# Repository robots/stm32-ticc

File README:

#STM32 based TICC

This project is based on TAPR's TICC project.

## Hardware

The frontend for time capture is copied from their schematic. Change has been done to input PICDIV that is responsible for coarse clock generation.

Original design uses pic12f675. For this design I have used pic12f1572. The software differences are only minor - few bank switch instructions. Hardware differense is almost none. Functional
difference is yet to be determined. But I dont think that the deterministic behavior of PIC has been changed.

Workhorse has been changed from ATMEGA to something more recent. I have used STM32F042.

This MCU has integrated 48MHz oscillator with clock recovery from USB, USB peripheral, lots of flash/ram for such simple project.

## Software

TICC presents on USB as ACM device. This works without any additional driver on linux. For windows i dont know - you will probably need ST's ACM driver. (google is your friend)

To connect use any terminal emulator you like - windows: realterm, teraterm, hyperterminal, ... for linux: minicom, screen, tio. Set speed to something reasonable (eg. 921600) and hit enter.

You should be presented with command line prompt ">".

Commands are:

help - prints help
reboot - reboots board
dfu - switches mcu to dfu mode. Carefull, you will need dfu-util to bring device back to live.
cfg - configuration submenu

cfg show - prints current configuration
cfg set xx blabla - sets variable "xx" to value "blabla"
cfg save - saves configuration to eeprom (not working yet)

Most configuration options are same as TICC, for more info refer to their documentation.

# Building
You will need gnuarm toolchain, gnu make and dfu-util.

Make sure that you have arm toolchain in PATH, enter "main" directory, and type "make bin".

To write the firmware to board use "dfu.sh" script. This script does two things: writes firmware and writes options to exit dfu mode.

# Credits
Software has been mostly written from scratch except for:
- usb stack, stdlibrary - from ST
- time interval calculation routines and TDC7200 driver  - from original TICC project, mostly rewritten or adapted for better readability - https://github.com/TAPR/TICC
- tfprintf - Copyright (C) 2004,2012  Kustaa Nyholm http://www.sparetimelabs.com/tinyprintf/index.html

Hardware:
- based on https://github.com/TAPR/TICC

# License
All files written by me are released to public domain. Use as you please. It would be nice to reference original repository if you do.

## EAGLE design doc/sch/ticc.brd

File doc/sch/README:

In this directory:

ticc.* - schematic/board layout for TICC
picdiv.* - schematic/board layout for simple PICDIV board.

There is absolutely no warranty and not support for these boards. While there are few working examples of this design I dont have time or resources for support.

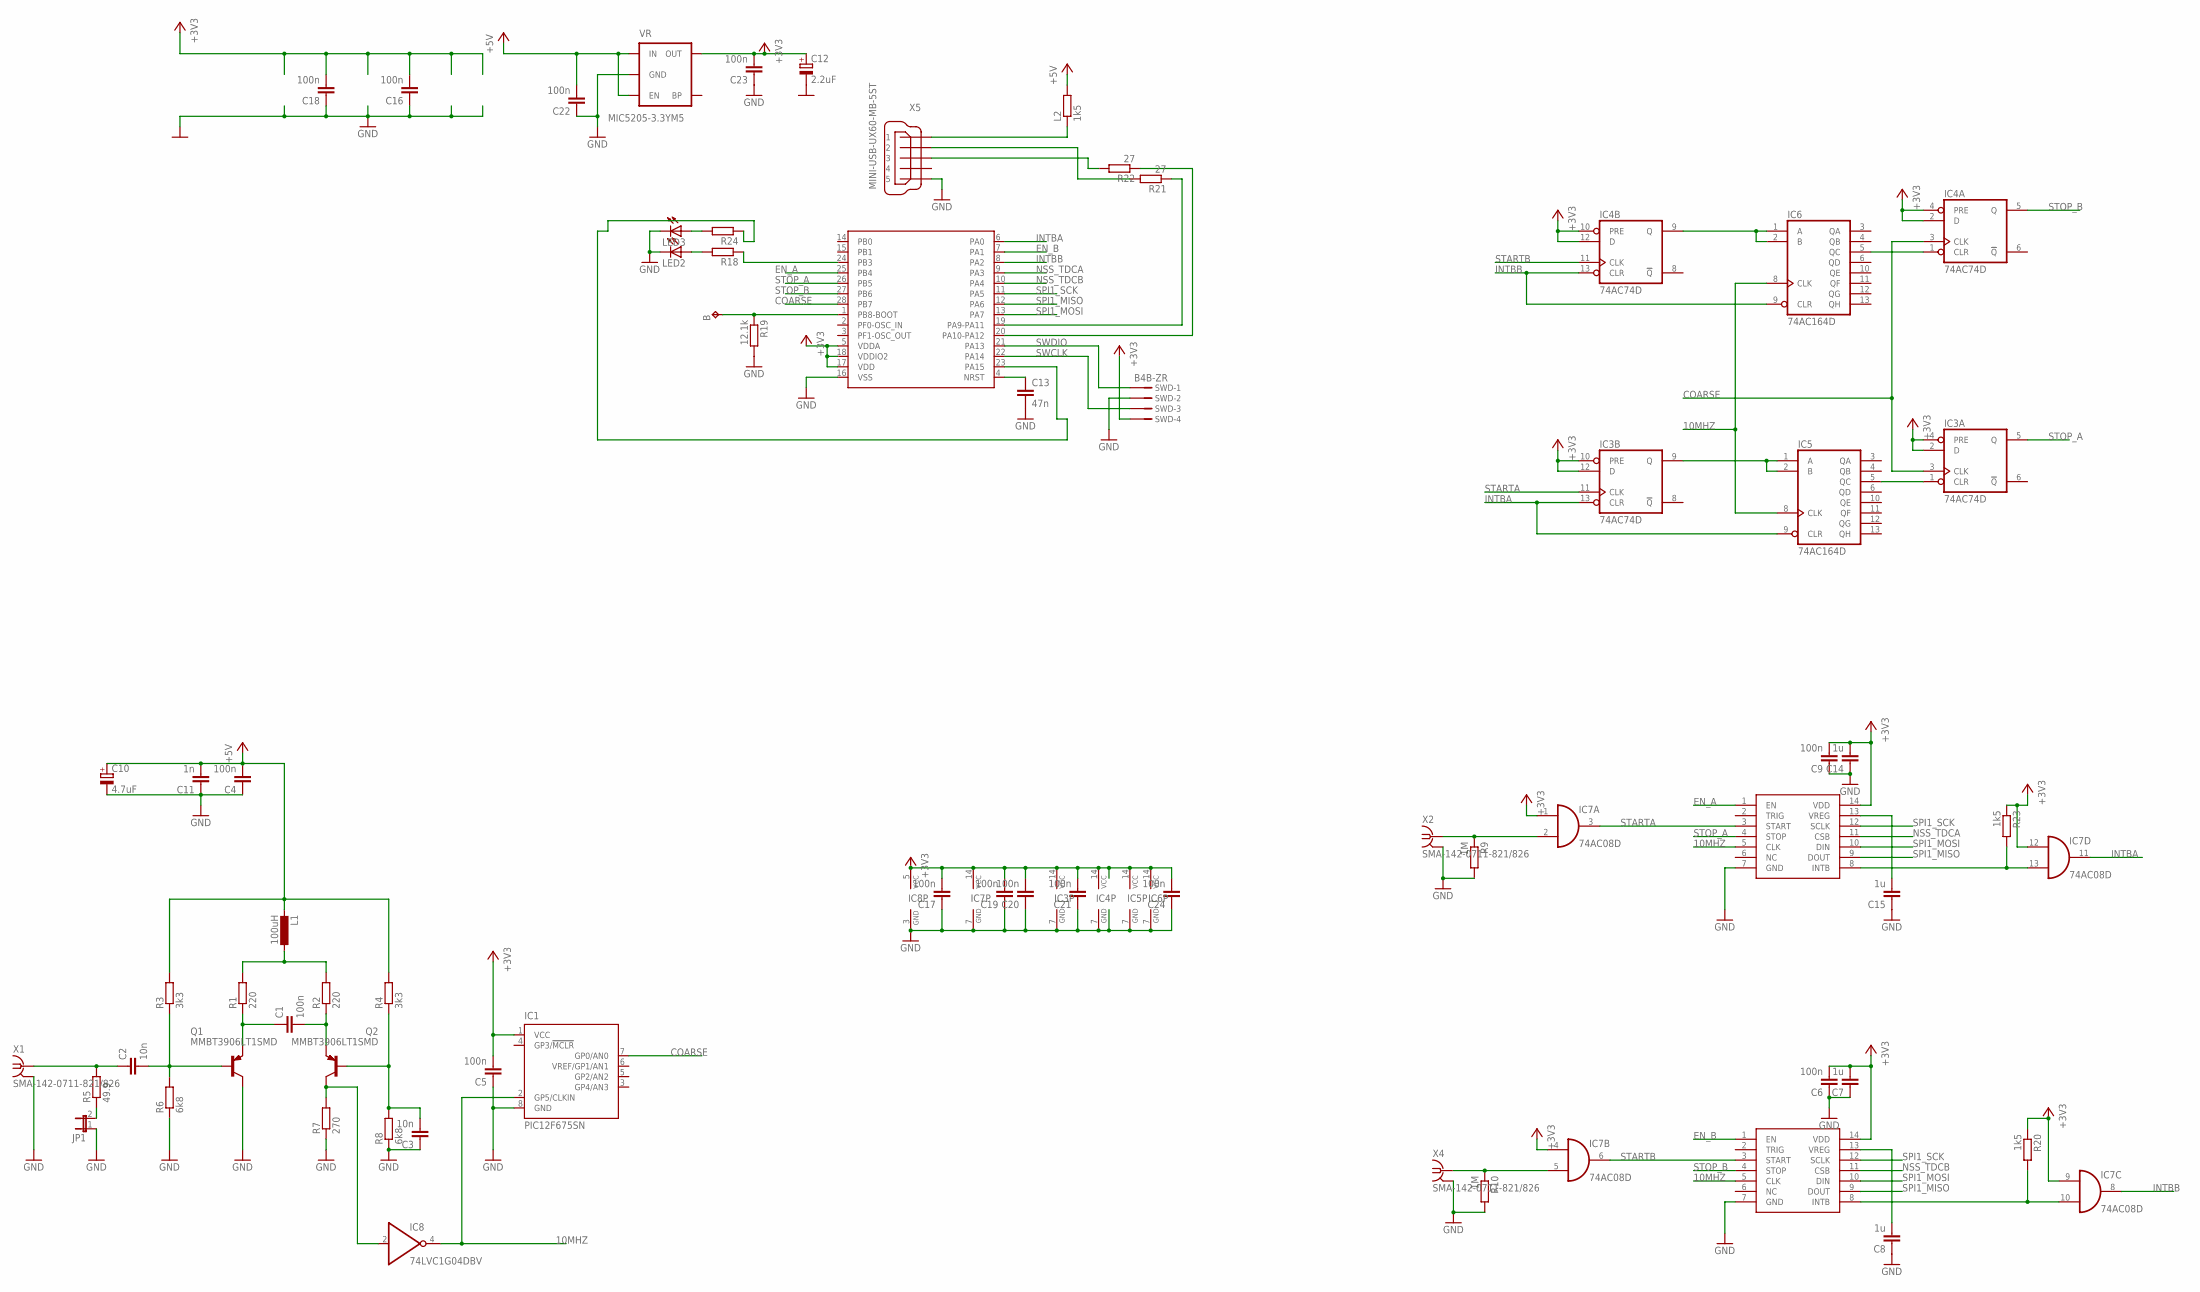
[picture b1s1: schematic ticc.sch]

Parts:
B: TPB1,27; B1,27
C1, C4, C5, C6, C9, C16, C17, C18, C19, C20, C21, C24: 100n; C0603
C2, C3: 10n; C0603
C7, C8, C14, C15: 1u; C0603
C10: 4.7uF; SMC_A
C11: 1n; C0603
C12: 2.2uF; SMC_A
C13: 47n; C0603
C22, C23: 100n; C0805K
IC1: PIC12F675SN; SO-08
IC3, IC4: 74AC74D; SO14
IC5, IC6: 74AC164D; SO14
IC7: 74AC08D; SO14
IC8: 74LVC1G04DBV; SOT23-5
JP1: JUMPER-2PTH; 1X02
L1: 100uH; L2012C
L2: 1k5; R0805
LED2, LED3: LEDCHIP-LED0805; CHIP-LED0805
Q1, Q2: MMBT3906LT1SMD; SOT23-BEC
R1, R2: 220; R0603
R3, R4: 3k3; R0603
R5: 49.9; R0603
R6, R8: 6k8; R0603
R7: 270; R0603
R9, R10: 1M; R0603
R18, R24: R-EU_R0603; R0603
R19: 12.1k; R0603
R20, R23: 1k5; R0603
R21, R22: 27; R0603
SWD: B4B-ZR
U$1: STM32F042G; QFN28
U$2, U$3: TDC7200; TSSOP14
VR: MIC5205-3.3YM5; SOT23-5
X1, X2, X4: SMA-142-0711-821/826; J502-ND-142-0711-821/826
X5: MINI-USB-UX60-MB-5ST; UX60-MB-5ST

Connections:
10MHZ: IC1.2 (GP5/CLKIN), IC5.8 (CLK), IC6.8 (CLK), IC8.4 (O), U$2.5 (CLK), U$3.5 (CLK)
+3V3: C5.2, C6.2, C7.2, C9.2, C12.+, C14.2, C16.2, C17.2, C18.2, C19.2, C20.2, C21.2, C23.2, C24.2, IC1.1 (VCC), IC3.2 (D), IC3.4 (PRE), IC3.10 (PRE), IC3.12 (D), IC3.14 (VCC), IC4.2 (D), IC4.4 (PRE), IC4.10 (PRE), IC4.12 (D), IC4.14 (VCC), IC5.14 (VCC), IC6.14 (VCC), IC7.1 (I0), IC7.4 (I0), IC7.9 (I0), IC7.12 (I0), IC7.14 (VCC), IC8.5 (VCC), R20.1, R23.1, SWD.4, U$1.5 (VDDA), U$1.17 (VDD), U$1.18 (VDDIO2), U$2.14 (VDD), U$3.14 (VDD), VR.5 (OUT)
+5V: C4.2, C10.+, C11.2, C22.2, L1.2, L2.2, R3.2, R4.2, VR.1 (IN), VR.3 (EN)
COARSE: IC1.7 (GP0/AN0), IC3.3 (CLK), IC4.3 (CLK), U$1.28 (PB7)
EN_A: U$1.25 (PB4), U$2.1 (EN)
EN_B: U$1.7 (PA1), U$3.1 (EN)
GND: C3.1, C4.1, C5.1, C6.1, C7.1, C8.1, C9.1, C10.-, C11.1, C12.-, C13.2, C14.1, C15.1, C16.1, C17.1, C18.1, C19.1, C20.1, C21.1, C22.1, C23.1, C24.1, IC1.8 (GND), IC3.7 (GND), IC4.7 (GND), IC5.7 (GND), IC6.7 (GND), IC7.7 (GND), IC8.3 (GND), JP1.1, LED2.C, LED3.C, Q1.C, R6.1, R7.1, R8.1, R9.2, R10.2, R19.2, SWD.2, U$1.16 (VSS), U$2.7 (GND), U$3.7 (GND), VR.2 (GND), X1.G@1 (GND), X1.G@2 (GND), X1.G@3 (GND), X1.G@4 (GND), X2.G@1 (GND), X2.G@2 (GND), X2.G@3 (GND), X2.G@4 (GND), X4.G@1 (GND), X4.G@2 (GND), X4.G@3 (GND), X4.G@4 (GND), X5.5
INTBA: IC3.13 (CLR), IC5.9 (CLR), IC7.11 (O), U$1.6 (PA0)
INTBB: IC4.13 (CLR), IC6.9 (CLR), IC7.8 (O), U$1.8 (PA2)
unnamed: C3.2, Q2.B, R4.1, R8.2
unnamed: JP1.2, R5.1
unnamed: C2.1, R5.2, X1.1
unnamed: C2.2, Q1.B, R3.1, R6.2
unnamed: L1.1, R1.2, R2.2
unnamed: C1.2, Q2.E, R2.1
unnamed: C1.1, Q1.E, R1.1
unnamed: R22.2, X5.3
unnamed: IC8.2 (I), Q2.C, R7.2
unnamed: IC7.2 (I1), R9.1, X2.1
unnamed: R21.2, X5.2
unnamed: IC7.5 (I1), R10.1, X4.1
unnamed: R18.1, U$1.24 (PB3)
unnamed: C15.2, U$2.13 (VREG)
unnamed: L2.1, X5.1
unnamed: R21.1, U$1.19 (PA9-PA11)
unnamed: IC3.1 (CLR), IC5.5 (QC)
unnamed: R22.1, U$1.20 (PA10-PA12)
unnamed: B.PP, R19.1, U$1.1 (PB8-BOOT)
unnamed: C13.1, U$1.4 (NRST)
unnamed: LED2.A, R18.2
unnamed: IC4.1 (CLR), IC6.5 (QC)
unnamed: IC3.9 (Q), IC5.1 (A), IC5.2 (B)
unnamed: IC4.9 (Q), IC6.1 (A), IC6.2 (B)
unnamed: R24.1, U$1.23 (PA15)
unnamed: IC7.10 (I1), R20.2, U$3.8 (INTB)
unnamed: IC7.13 (I1), R23.2, U$2.8 (INTB)
unnamed: LED3.A, R24.2
unnamed: C8.2, U$3.13 (VREG)
NSS_TDCA: U$1.9 (PA3), U$2.11 (CSB)
NSS_TDCB: U$1.10 (PA4), U$3.11 (CSB)
SPI1_MISO: U$1.12 (PA6), U$2.9 (DOUT), U$3.9 (DOUT)
SPI1_MOSI: U$1.13 (PA7), U$2.10 (DIN), U$3.10 (DIN)
SPI1_SCK: U$1.11 (PA5), U$2.12 (SCLK), U$3.12 (SCLK)
STARTA: IC3.11 (CLK), IC7.3 (O), U$2.3 (START)
STARTB: IC4.11 (CLK), IC7.6 (O), U$3.3 (START)
STOP_A: IC3.5 (Q), U$1.26 (PB5), U$2.4 (STOP)
STOP_B: IC4.5 (Q), U$1.27 (PB6), U$3.4 (STOP)
SWCLK: SWD.3, U$1.22 (PA14)
SWDIO: SWD.1, U$1.21 (PA13)

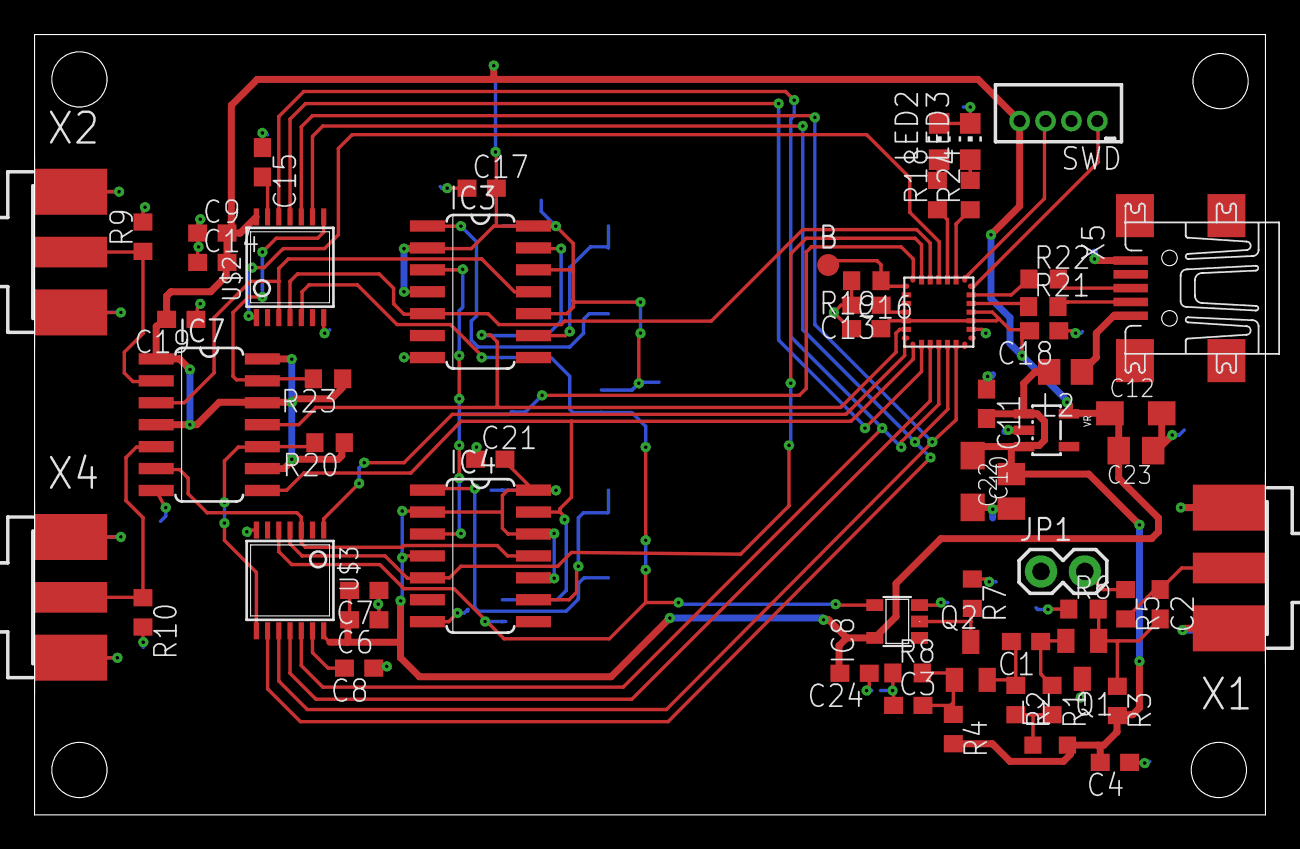
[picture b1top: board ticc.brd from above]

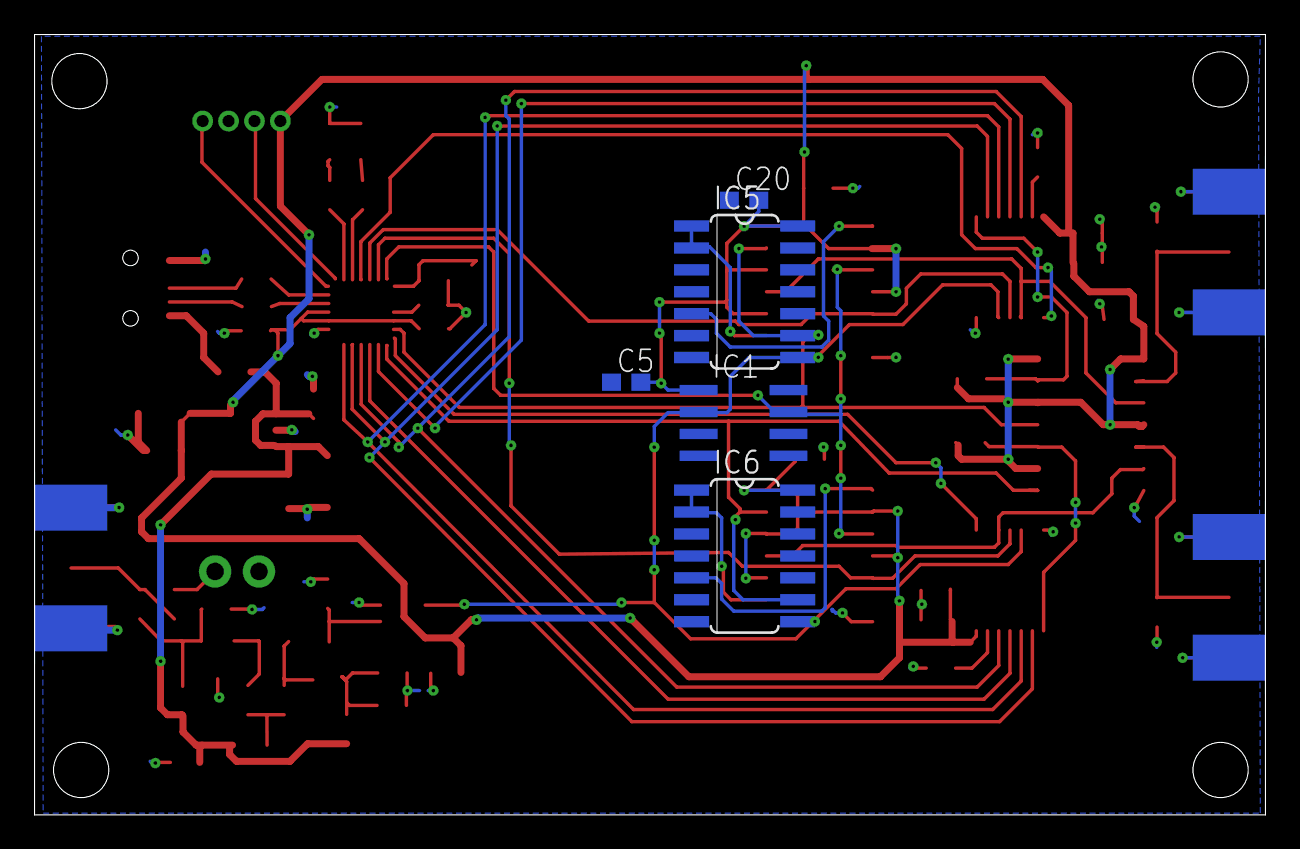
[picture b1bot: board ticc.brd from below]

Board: 2 copper layers, 71.3 x 45.2 mm, 65 parts (5 on the bottom side), 49 nets.

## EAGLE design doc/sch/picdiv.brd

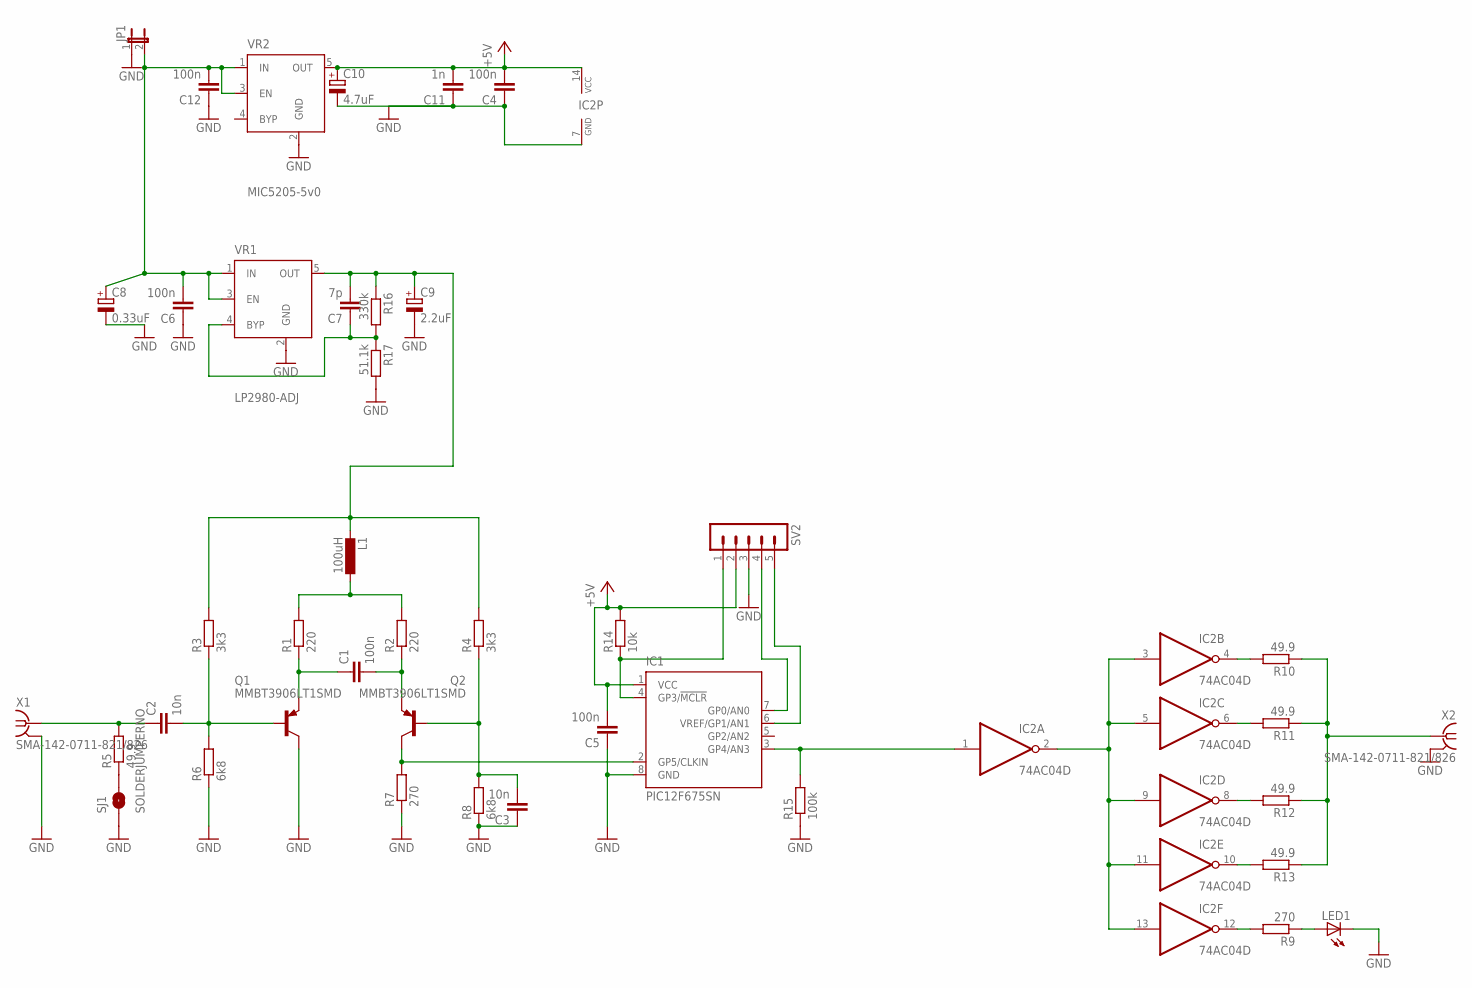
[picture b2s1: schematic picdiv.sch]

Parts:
C1, C4, C5, C6, C12: 100n; C0603
C2, C3: 10n; C0603
C7: 7p; C0603
C8: 0.33uF; SMC_A
C9: 2.2uF; SMC_A
C10: 4.7uF; SMC_A
C11: 1n; C0603
IC1: PIC12F675SN; SO-08
IC2: 74AC04D; SO14
JP1: JUMPER-2PTH; 1X02
L1: 100uH; L2012C
LED1: LEDCHIPLED_0603; CHIPLED_0603
Q1, Q2: MMBT3906LT1SMD; SOT23-BEC
R1, R2: 220; R0603
R3, R4: 3k3; R0603
R5, R10, R11, R12, R13: 49.9; R0603
R6, R8: 6k8; R0603
R7, R9: 270; R0603
R14: 10k; R0603
R15: 100k; R0603
R16: 330k; R0603
R17: 51.1k; R0603
SJ1: SOLDERJUMPERNO; SJ_2S-NO
SV2: MA05-1
VR1: LP2980-ADJ; SOT23-5
VR2: MIC5205-5v0; SOT23-5
X1, X2: SMA-142-0711-821/826; J502-ND-142-0711-821/826

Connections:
+5V: C4.2, C5.2, C10.+, C11.2, IC1.1 (VCC), IC2.14 (VCC), R14.2, SV2.2, VR2.5 (OUT)
+8V: C7.2, C9.+, L1.2, R3.2, R4.2, R16.1, VR1.5 (OUT)
GND: C3.1, C4.1, C5.1, C6.1, C8.-, C9.-, C10.-, C11.1, C12.1, IC1.8 (GND), IC2.7 (GND), JP1.1, LED1.C, Q1.C, R6.1, R7.1, R8.1, R15.1, R17.2, SJ1.1, SV2.3, VR1.2 (GND), VR2.2 (GND), X1.G@1 (GND), X1.G@2 (GND), X1.G@3 (GND), X1.G@4 (GND), X2.G@1 (GND), X2.G@2 (GND), X2.G@3 (GND), X2.G@4 (GND)
unnamed: C3.2, Q2.B, R4.1, R8.2
unnamed: R5.1, SJ1.2
unnamed: C2.1, R5.2, X1.1
unnamed: C2.2, Q1.B, R3.1, R6.2
unnamed: L1.1, R1.2, R2.2
unnamed: C1.2, Q2.E, R2.1
unnamed: C1.1, Q1.E, R1.1
unnamed: IC1.2 (GP5/CLKIN), Q2.C, R7.2
unnamed: IC2.12 (O), R9.2
unnamed: LED1.A, R9.1
unnamed: IC2.2 (O), IC2.3 (I), IC2.5 (I), IC2.9 (I), IC2.11 (I), IC2.13 (I)
unnamed: IC2.10 (O), R13.2
unnamed: IC2.4 (O), R10.2
unnamed: IC2.6 (O), R11.2
unnamed: IC2.8 (O), R12.2
unnamed: IC1.4 (GP3/!MCLR), R14.1, SV2.1
unnamed: C6.2, C8.+, C12.2, JP1.2, VR1.1 (IN), VR1.3 (EN), VR2.1 (IN), VR2.3 (EN)
unnamed: IC1.7 (GP0/AN0), SV2.4
unnamed: IC1.6 (VREF/GP1/AN1), SV2.5
OUT: R10.1, R11.1, R12.1, R13.1, X2.1
PICOUT: IC1.3 (GP4/AN3), IC2.1 (I), R15.2
VADJ: C7.1, R16.2, R17.1, VR1.4 (BYP)

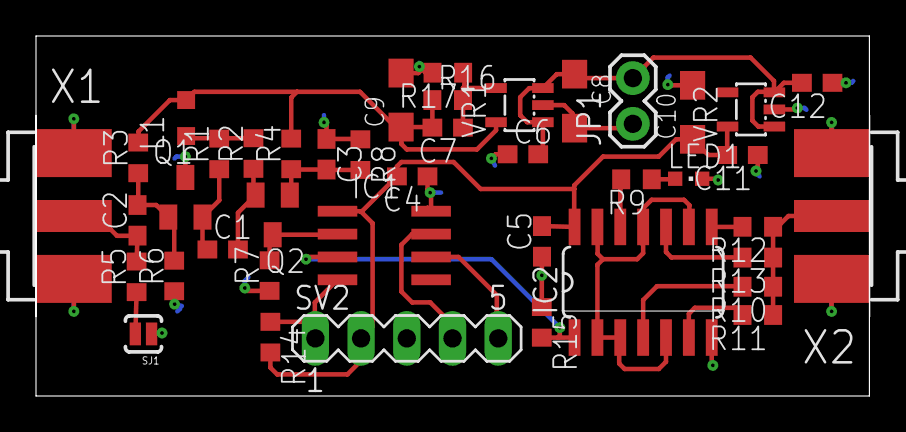
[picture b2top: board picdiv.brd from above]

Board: 2 copper layers, 46.3 x 20.0 mm, 42 parts (0 on the bottom side), 25 nets.

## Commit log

2019-11-29 Initial commit of public version
2019-11-29 Add missing option bytes.
2020-10-06 add missing picdiv files.
2024-12-21 update gpio driver
2024-12-21 console: remove warnings
2024-12-21 cleanup configuration and clock period calculation
2024-12-21 main: add missing include
2024-12-21 add () to define

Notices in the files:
parts and their libraries:
SparkFun: Licensing: CC v3.0 Share-Alike You are welcome to use this library for commercial purposes.
